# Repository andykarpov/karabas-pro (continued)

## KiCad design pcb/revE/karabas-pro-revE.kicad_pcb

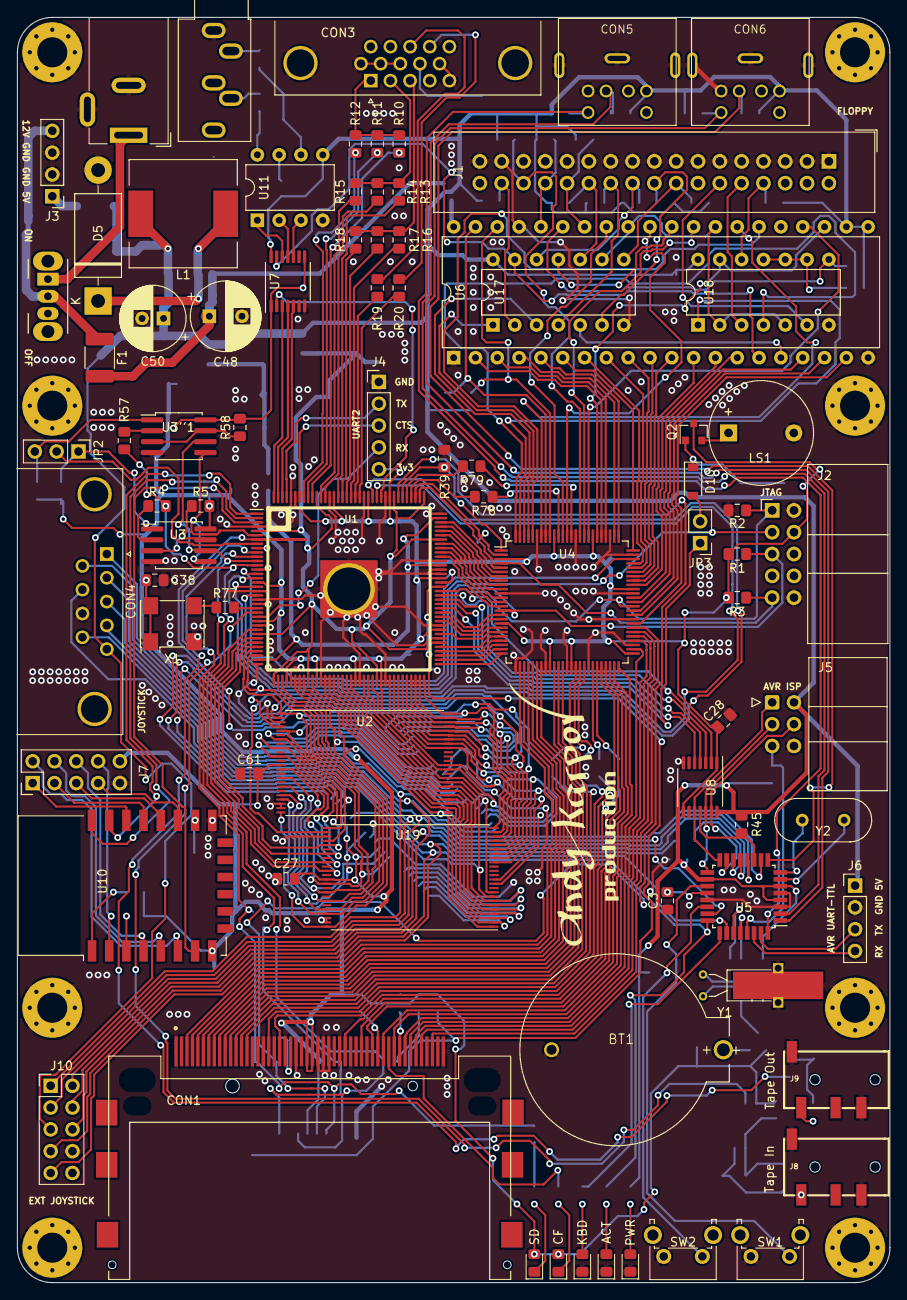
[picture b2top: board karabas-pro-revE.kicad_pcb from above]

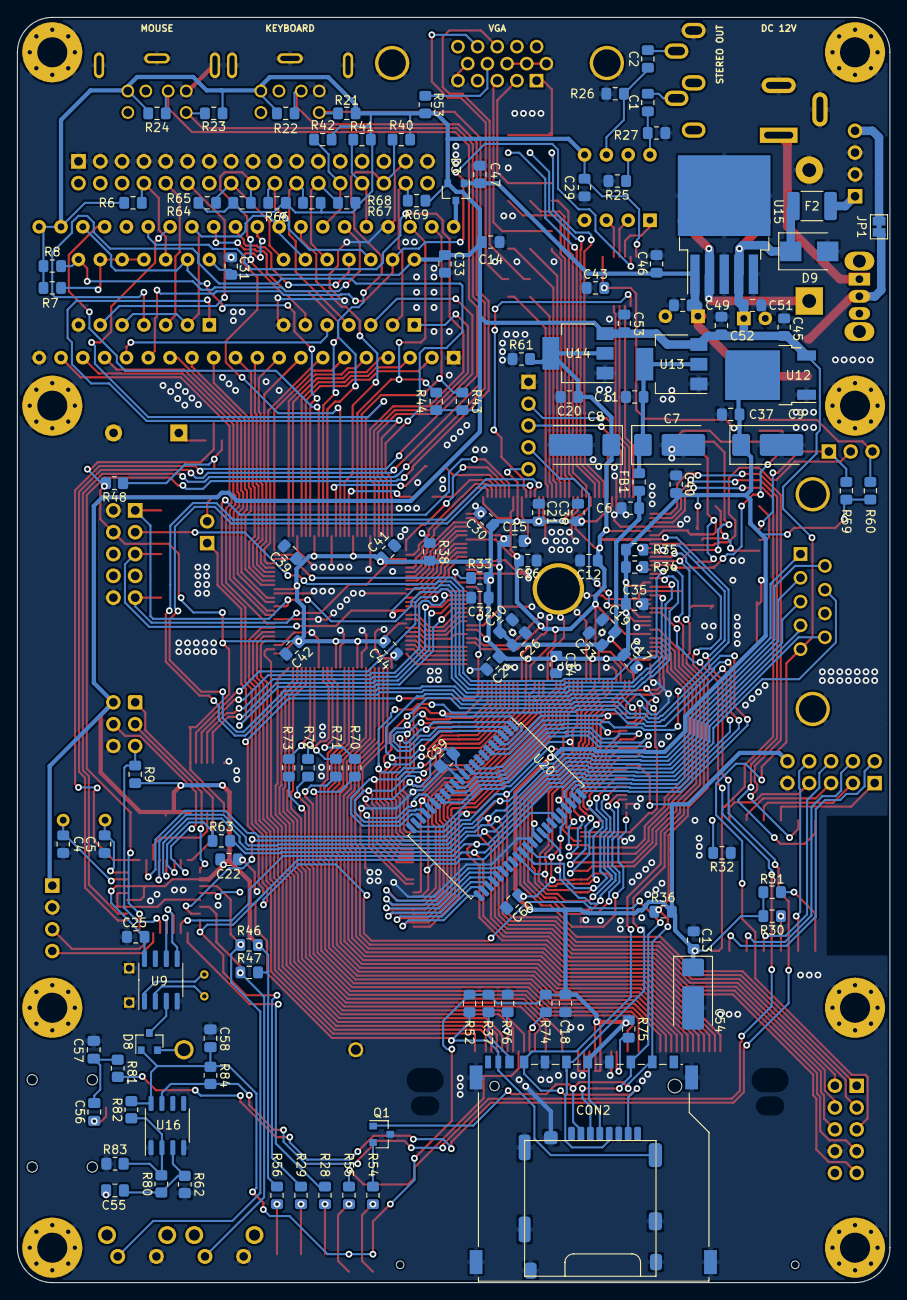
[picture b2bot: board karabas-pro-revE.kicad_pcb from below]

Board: 2 copper layers, 101.6 x 147.3 mm, 217 parts (128 on the bottom side), 272 nets.

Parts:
BT1: 3V; BAT_BS-7-BLUE
C1, C2: 10uF; C_0805_2012Metric_Pad1.15x1.40mm_HandSolder
C3, C10: 1uF; C_0805_2012Metric_Pad1.15x1.40mm_HandSolder
C4, C5: 22p; C_0805_2012Metric_Pad1.15x1.40mm_HandSolder
C6: 1n; C_0805_2012Metric_Pad1.15x1.40mm_HandSolder
C7, C8, C9: 10uF; CP_EIA-7343-31_Kemet-D-uni
C11, C12, C13, C14, C15, C16, C17, C18, C19, C20, C21, C22, C23, C24, C25, C26, C27, C28, C29, C30, C31, C32, C33, C34, C35, C36, C37, C38, C39, C40, C41, C42, C43, C44, C45, C46, C47, C49, C51, C52, C53: 100n; C_0805_2012Metric_Pad1.15x1.40mm_HandSolder
C48: 470uF; CP_Radial_D8.0mm_P3.80mm
C50: 220uF; CP_Radial_D7.5mm_P2.50mm
C54: 100uF; CP_EIA-7343-31_Kemet-D-uni
C55, C56, C58, C59, C60, C61: 100n; C_0805_2012Metric_Pad1.18x1.45mm_HandSolder
C57: 3n3; C_0805_2012Metric_Pad1.18x1.45mm_HandSolder
CON1: CF-CARD; TE_1734451-1-LONG
CON2: SD; SD_TE_2041021-mod
CON3: VGA; DSUB-15-HD_Female_Horizontal_P2.29x1.98mm_EdgePinOffset3.03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
CON4: Joystick; DSUB-9_Male_Horizontal_P2.77x2.84mm_EdgePinOffset7.70mm_Hou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
CON5: Keyboard; MINI_DIN_6_33PRIMARY
CON6: Mouse; MINI_DIN_6_33PRIMARY
CON7: Audio; Jack_3.5mm_CUI_SJ1-3535NG_Horizontal
CON8: 12V; BarrelJack_Wuerth_6941xx301002
CON9: MicroSD'; MICRO_SD_MOLEX
D1: KBD; LED_0805_2012Metric_Pad1.15x1.40mm_HandSolder
D2: ACT; LED_0805_2012Metric_Pad1.15x1.40mm_HandSolder
D3, D8: BAT54C; SOT-23
D4: SD; LED_0805_2012Metric_Pad1.15x1.40mm_HandSolder
D5: 1N5820; D_DO-201AD_P15.24mm_Horizontal
D6: CF; LED_0805_2012Metric_Pad1.15x1.40mm_HandSolder
D7: PWR; LED_0805_2012Metric_Pad1.15x1.40mm_HandSolder
D9: SM6T6V8A; D_SMB
D10: 1N4148W; D_SOD-123
F1, F2: Polyfuse_Small; Fuse_1812_4532Metric_Castellated
FB1: Ferrite_Bead; L_0805_2012Metric_Pad1.15x1.40mm_HandSolder
H1, H2, H3, H4, H5, H6, H7, H8: MountingHole; MountingHole_3.5mm_Pad_Via
J1: Floppy; IDC-Header_2x17_P2.54mm_Vertical
J2: FPGA JTAG; IDC-Header_2x05_P2.54mm_Horizontal
J3: Floppy; PinHeader_1x04_P2.54mm_Vertical
J4: UART2; PinHeader_1x05_P2.54mm_Vertical
J5: AVR JTAG; IDC-Header_2x03_P2.54mm_Horizontal
J6: AVR UART; PinHeader_1x04_P2.54mm_Vertical
J7: ESP-BUS; PinHeader_2x05_P2.54mm_Vertical
J8: Tape In; AUDIO_JACK_3.5MM_SMD_TRRS
J9: Tape Out; AUDIO_JACK_3.5MM_SMD_TRRS
J10: Ext Joystick; PinHeader_2x05_P2.54mm_Vertical
JP1: 12V EN; SolderJumper-2_P1.3mm_Bridged_Pad1.0x1.5mm
JP2: Flash 1/2; PinHeader_1x03_P2.54mm_Vertical
JP3: Beeper enabled; PinHeader_1x02_P2.54mm_Vertical
L1: 68uH; L_12x12mm_H6mm
LS1: Beeper; Buzzer_12x9.5RM7.6
Q1: BC856; SOT-23
Q2: BC847; SOT-23
R1, R2, R3: 2k4; R_0805_2012Metric_Pad1.15x1.40mm_HandSolder
R4, R57, R77, R78, R79: 27; R_0805_2012Metric_Pad1.15x1.40mm_HandSolder
R5, R9, R30, R31, R33, R34, R35, R36, R37, R38, R39, R40, R41, R42, R43, R44, R45, R46, R47, R52, R58, R59, R60: 10k; R_0805_2012Metric_Pad1.15x1.40mm_HandSolder
R6, R11, R14, R17, R74, R75, R76: 1k; R_0805_2012Metric_Pad1.15x1.40mm_HandSolder
R7, R8, R21, R22, R23, R24: 4k7; R_0805_2012Metric_Pad1.15x1.40mm_HandSolder
R10, R13, R16: 2k; R_0805_2012Metric_Pad1.15x1.40mm_HandSolder
R12, R15, R18: 510; R_0805_2012Metric_Pad1.15x1.40mm_HandSolder
R19, R20: 75; R_0805_2012Metric_Pad1.15x1.40mm_HandSolder
R25: 820; R_0805_2012Metric_Pad1.15x1.40mm_HandSolder
R26, R27: 750; R_0805_2012Metric_Pad1.15x1.40mm_HandSolder
R28, R29, R54, R55, R56: 470; R_0805_2012Metric_Pad1.15x1.40mm_HandSolder
R32: 33; R_0805_2012Metric_Pad1.15x1.40mm_HandSolder
R48: 15k*; R_0805_2012Metric_Pad1.20x1.40mm_HandSolder
R53: X*; R_0805_2012Metric_Pad1.15x1.40mm_HandSolder
R61: 300; R_0805_2012Metric_Pad1.15x1.40mm_HandSolder
R62: 1M; R_0805_2012Metric_Pad1.20x1.40mm_HandSolder
R63, R70, R71, R72, R73: 100; R_0805_2012Metric_Pad1.15x1.40mm_HandSolder
R64, R65, R66, R67, R68, R69: 330; R_0805_2012Metric_Pad1.15x1.40mm_HandSolder
R80: 5k1; R_0805_2012Metric_Pad1.20x1.40mm_HandSolder
R81: 33k; R_0805_2012Metric_Pad1.20x1.40mm_HandSolder
R82, R83, R84: 1k; R_0805_2012Metric_Pad1.20x1.40mm_HandSolder
SW1, SW2: SW_Push; SW_Tactile_SPST_Angled_PTS645Vx58-2LFS
SW4: SW_SPST; SW_CuK_OS102011MA1QN1_SPDT_Angled
U1: EP4CE10E22C8N; ALTERA-QFP-145
U2, U19: CY62167EV30LL; TSOP-I-48_18.4x12mm_P0.5mm
U3, U3''1: W25Q16; SOIC-8_5.23x5.23mm_P1.27mm-LONG
U4: EPM3128ATC100-10N; LQFP-100_14x14mm_P0.5mm
U5: ATMEGA328-AU; TQFP-32_7x7mm_P0.8mm
U6: MB8877A; DIP-40_W15.24mm
U7, U8: TXB0104PW; TSSOP-14_4.4x5mm_P0.65mm
U9: DS1307Z+; SOIC-8_3.9x4.9mm_P1.27mm
U10: ESP-12E
U11: TDA1543; DIP-8_W7.62mm
U12: AMS1117-3.3; TO-252-2
U13: AMS1117-2.5; SOT-223-3_TabPin2
U14: AMS1117-1.2; SOT-223-3_TabPin2
U15: LM2596S-5; TO-263-5_TabPin3
U16: LM311; SO-8_3.9x4.9mm_P1.27mm
U17: 74LS06; DIP-14_W7.62mm
U18: 74LS38; DIP-14_W7.62mm
U20: BS62LV1600; TSOP-II-44_10.16x18.41mm_P0.8mm
X1: SG-7050CAN; Oscillator_SMD_SeikoEpson_SG8002CA-4Pin_7.0x5.0mm
Y1: 32768Hz; Crystal_AT310_D3.0mm_L10.0mm_Horizontal_1EP_style2
Y2: 16MHz; Crystal_HC49-U_Vertical

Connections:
+12V: C46.1, C47.1, C48.1, C49.1, D3.1, F1.2, U15.1
/ASDO: U1.6, U3.5, U3''1.5
/AVR_MISO: J5.1, U5.16, U8.10
/AVR_MOSI: J5.4, U5.15, U8.13
/AVR_RX: J6.4, U5.30
/AVR_SCK: J5.3, U5.17, U8.12
/AVR_TX: J6.3, U5.31
/AVR_XT1: C4.2, U5.7, Y2.1
/AVR_XT2: C5.2, U5.8, Y2.2
/B: CON3.3, R16.2, R17.2, R18.2
/BEEPER: JP3.1, U1.86
/BTN1: R46.1, SW1.1, U5.19
/BTN2: R47.1, SW2.1, U5.22
/CLK_50MHZ: R77.2, U1.23
/CONF_DONE: R33.1, U1.92
/CPLD_CLK: R79.2, U1.113
/CPLD_CLK2: R78.2, U1.112
/D0: U4.72, U6.7
/D1: U4.71, U6.8
/D2: U4.70, U6.9
/D3: U4.69, U6.10
/D4: U4.68, U6.11
/D5: U4.67, U6.12
/D6: U4.64, U6.13
/D7: U4.63, U6.14
/DATA0: CON2.7, CON9.7, R4.2, R57.2, U1.13
/DCLK: CON2.5, CON9.5, U1.12, U3.6, U3''1.6
/ESP_ADC: J7.8, U10.2
/ESP_GPIO0: J7.5, U10.18
/ESP_GPIO2: J7.7, U10.17
/ESP_GPIO4: J7.3, U10.19
/ESP_GPIO5: J7.1, U10.20
/ESP_GPIO12: J7.2, U10.6
/ESP_GPIO14: J7.4, U10.5
/ESP_GPIO16: J7.6, U10.4
/FDC_A0: U4.76, U6.5
/FDC_A1: U4.75, U6.6
/FDC_CLK: U4.83, U6.24
/FDC_DIR: U6.16, U17.5
/FDC_DRQ: R44.1, U4.92, U6.38
/FDC_DS0: U4.99, U18.1
/FDC_DS1: U4.100, U18.4
/FDC_HLT: U4.81, U6.23, U18.13
/FDC_INTRQ: R43.1, U4.93, U6.39
/FDC_IP: R8.2, U6.35, U18.8
/FDC_RCLK: U4.96, U6.26
/FDC_RDY: U6.28, U6.32, U17.9, U18.2, U18.5
/FDC_SIDE: J1.32, R69.2, U17.2
/FDC_SL: U4.61, U6.17
/FDC_SR: U4.60, U6.18
/FDC_STEP: U6.15, U7.13, U17.13
/FDC_TR43: U4.84, U6.29
/FDC_WD: U4.88, U6.31
/FDC_WDATA: U4.98, U17.3
/FDC_WF_DE: U4.89, U6.33
/FDC_WGATE: U6.30, U17.11
/G: CON3.2, R13.2, R14.2, R15.2
/HS: CON3.13, R19.1
/I2C_SCL: U5.28, U9.6
/I2C_SDA: U5.27, U9.5
/JOY_DOWN: CON4.2, J10.2, U5.12
/JOY_FIRE1: CON4.6, J10.6, U5.23
/JOY_FIRE2: CON4.9, J10.9, U5.26
/JOY_LEFT: CON4.3, J10.3, U5.13
/JOY_R2: CON4.4, J10.4, R63.2
/JOY_RIGHT: R63.1, U5.14
/JOY_UP: CON4.1, J10.1, U5.10
/L1: D1.2, R28.2
/L2: D2.2, R29.2
/L3: D7.2, R56.2
/L4: D4.1, R54.2
/L5: D6.1, R55.2
/LAVR_MISO: U1.87, U8.5
/LAVR_MOSI: U1.90, U8.2
/LAVR_SCK: U1.89, U8.3
/LED1: R28.1, U5.25
/LED2: CON4.7, J10.7, R29.1, U5.24
/LED_BUSY: CON1.45, R55.1
/LFDC_STEP: U1.119, U7.2
/LSND_BS: U1.144, U7.3
/LSND_DAT: U1.142, U7.5
/LSND_WS: U1.143, U7.4
/MA0: U1.33, U2.25, U19.25, U20.5
/MA1: U1.72, U2.24, U19.24, U20.4
/MA2: U1.71, U2.23, U19.23, U20.3
/MA3: U1.70, U2.22, U19.22, U20.2
/MA4: U1.69, U2.21, U19.21, U20.1
/MA5: U1.68, U2.20, U19.20, U20.44
/MA6: U1.67, U2.19, U19.19, U20.43
/MA7: U1.66, U2.18, U19.18, U20.42
/MA8: U1.58, U2.8, U19.8, U20.39
/MA9: U1.55, U2.7, U19.7, U20.28
/MA10: U1.54, U2.6, U19.6, U20.27
/MA11: U1.53, U2.5, U19.5, U20.26
/MA12: U1.52, U2.4, U19.4, U20.25
/MA13: U1.51, U2.3, U19.3, U20.24
/MA14: U1.50, U2.2, U19.2, U20.23
/MA15: U1.49, U2.1, U19.1, U20.22
/MA16: U1.46, U2.48, U19.48, U20.21
/MA17: U1.65, U2.17, U19.17, U20.20
/MA18: U1.64, U2.16, U19.16, U20.19
/MA19: U1.59, U2.9, U19.9, U20.18
/MA20: U1.44, U2.45, U19.45, U20.16
/MD0: U1.32, U2.29, U19.29, U20.9
/MD1: U1.31, U2.31, U19.31, U20.10
/MD2: U1.30, U2.33, U19.33, U20.13
/MD3: U1.28, U2.35, U19.35, U20.14
/MD4: U1.38, U2.38, U19.38, U20.31
/MD5: U1.39, U2.40, U19.40, U20.32
/MD6: U1.42, U2.42, U19.42, U20.35
/MD7: U1.43, U2.44, U19.44, U20.36
/NCONFIG: R34.1, U1.14
/NCSO: JP2.2, U1.8
/NCSO1: JP2.1, R59.1, U3.1
/NCSO2: JP2.3, R60.1, U3''1.1
/NSTATUS: R35.1, U1.9
/PS2_KB_CLK: CON5.5, R21.1, U5.32
/PS2_KB_DATA: CON5.1, R22.1, U5.2
/PS2_MS_CLK: CON6.5, R23.1, U5.1
/PS2_MS_DATA: CON6.1, R24.1, U5.9
/R: CON3.1, R10.2, R11.2, R12.2
/SA0: U1.110, U4.5
/SA1: U1.106, U4.6
/SD0: U1.105, U4.7
/SD1: U1.104, U4.8
/SD2: U1.103, U4.9
/SD3: U1.101, U4.10
/SD4: U1.100, U4.12
/SD5: U1.99, U4.13
/SD6: U1.98, U4.14
/SD7: U1.85, U4.16
/SD8: U1.84, U4.17
/SD9: U1.83, U4.19
/SD10: U1.80, U4.20
/SD11: U1.77, U4.21
/SD12: U1.76, U4.22
/SD13: U1.75, U4.23
/SD14: U1.74, U4.24
/SD15: U1.73, U4.25
/SDIR: R38.1, U1.111, U4.2
/SD_DI: CON2.2, CON9.3, U1.115
/SND_BS: U7.12, U11.1
/SND_DAT: U7.10, U11.3
/SND_L: C2.2, CON7.T
/SND_R: C1.2, CON7.R
/SND_WS: U7.11, U11.2
/TCK: J2.1, R2.2, U1.16, U4.62
/TDI: J2.9, R3.1, U4.4
/TDI1: U1.15, U4.73
/TDO: J2.3, U1.20
/TMS: J2.5, R1.1, U1.18, U4.15
/UART2_CTS: J4.3, U1.138
/UART2_RX: J4.4, U1.25
/UART2_TX: J4.2, U1.141
/UART_CTS: U1.3, U10.7
/UART_RX: U1.2, U10.22
/UART_TX: U1.1, U10.21
/VGA_B0: R16.1, U1.126
/VGA_B1: R17.1, U1.127
/VGA_B2: R18.1, U1.128
/VGA_G0: R13.1, U1.129
/VGA_G1: R14.1, U1.132
/VGA_G2: R15.1, U1.133
/VGA_HS: R19.2, U1.125
/VGA_R0: R10.1, U1.135
/VGA_R1: R11.1, U1.136
/VGA_R2: R12.1, U1.137
/VGA_VS: R20.2, U1.124
/VS: CON3.14, R20.1
/WA0: CON1.20, U4.49
/WA1: CON1.19, U4.48
/WA2: CON1.18, U4.47
/WD0: CON1.21, U4.50
/WD1: CON1.22, U4.52
/WD2: CON1.23, U4.55
/WD3: CON1.2, U4.27
/WD4: CON1.3, U4.29
/WD5: CON1.4, U4.31
/WD6: CON1.5, U4.35
/WD7: CON1.6, U4.37
/WD8: CON1.47, U4.54
/WD9: CON1.48, U4.56
/WD10: CON1.49, U4.57
/WD11: CON1.27, U4.28
/WD12: CON1.28, U4.30
/WD13: CON1.29, U4.32
/WD14: CON1.30, U4.36
/WD15: CON1.31, U4.40
/~AVR_CS: R45.1, U5.11, U8.11
/~AVR_RESET: J5.5, R9.1, U5.29
/~FDC_CS: U4.79, U6.3
/~FDC_DIR: J1.18, R65.2, U17.6
/~FDC_DRIVE0: J1.10, U18.3
/~FDC_DRIVE1: J1.12, U18.6
/~FDC_INDEX: J1.8, R6.2, U18.12
/~FDC_MOTOR: J1.16, R64.2, U17.8
/~FDC_RAWR: U4.94, U6.27
/~FDC_RDATA: J1.30, R40.1, U4.85
/~FDC_RST: U4.58, U6.19
/~FDC_SIDE: U4.97, U17.1
/~FDC_STEP: J1.20, R66.2, U17.12
/~FDC_TR00: J1.26, R42.1, U6.34
/~FDC_WDATA: J1.22, R67.2, U17.4
/~FDC_WGATE: J1.24, R68.2, U17.10
/~FDC_WPRT: J1.28, R41.1, U6.36
/~LAVR_CS: U1.88, U8.4
/~LWCS0: R70.1, U4.41
/~LWCS1: R71.1, U4.42
/~LWRD: R72.1, U4.44
/~LWWR: R73.1, U4.45
/~MRD: U1.34, U2.28, U19.28, U20.41
/~MWR: U1.60, U2.11, U19.11, U20.17
/~RAMCE1: U1.121, U2.26
/~RAMCE2: U1.120, U19.26
/~RAMCE3: U1.7, U20.6
/~RD: U4.77, U6.4
/~RESET: R39.1, U1.114, U4.1
/~SD_CS: CON2.1, CON9.2, Q1.1, R36.1, U1.11
/~SD_DET: CON2.10, CON9.9, R52.1, U1.91
/~WCS0: CON1.7, R70.2
/~WCS1: CON1.32, R71.2
/~WR: U4.80, U6.2
/~WRD: CON1.34, R72.2
/~WRESET: CON1.41, U4.46
/~WWR: CON1.35, R73.2
GND: BT1.2, C3.1, C4.1, C5.1, C6.2, C7.2, C8.2, C9.2, C10.2, C11.2, C12.2, C13.2, C14.2, C15.2, C16.2, C17.2, C18.2, C19.2, C20.2, C21.2, C22.2, C23.2, C24.2, C25.2, C26.2, C27.2, C28.2, C29.2, C30.2, C31.2, C32.2, C33.2, C34.2, C35.2, C36.2, C37.2, C38.2, C39.2, C40.2, C41.2, C42.2, C43.2, C44.2, C45.2, C46.2, C47.2, C48.2, C49.2, C50.2, C51.2, C52.2, C53.2, C54.2, C57.1, C58.2, C59.2, C60.2, C61.2, CON1.1, CON1.8, CON1.9, CON1.10, CON1.11, CON1.12, CON1.14, CON1.15, CON1.16, CON1.17, CON1.39, CON1.50, CON2.3, CON2.6, CON2.12, CON2.13, CON3.0, CON3.5, CON3.6, CON3.7, CON3.8, CON3.10, CON4.0, CON4.8, CON5.3, CON5.GND, CON6.3, CON6.GND, CON7.S, CON8.2, CON8.3, CON9.6, CON9.10, CON9.11, CON9.12, CON9.13, CON9.14, CON9.15, D1.1, D2.1, D5.2, D7.1, D9.2, H1.1, H2.1, H3.1, H4.1, H5.1, H6.1, H7.1, H8.1, J1.1, J1.3, J1.5, J1.7, J1.9, J1.11, J1.13, J1.15, J1.17, J1.19, J1.21, J1.23, J1.25, J1.27, J1.29, J1.31, J1.33, J2.2, J2.10, J3.2, J3.3, J4.1, J5.6, J6.2, J7.9, J8.R2, J8.S, J9.R2, J9.S, J10.8, LS1.2, Q1.3, R2.1, R25.2, R26.2, R27.2, R32.1, R39.2, R61.1, R62.2, R76.2, R83.2, SW1.2, SW2.2, U1.4, U1.19, U1.21, U1.22, U1.27, U1.36, U1.41, U1.48, U1.57, U1.63, U1.79, U1.82, U1.94, U1.95, U1.97, U1.108, U1.118, U1.123, U1.131, U1.140, U1.145, U2.27, U2.46, U2.47, U3.4, U3''1.4, U4.11, U4.26, U4.33, U4.38, U4.43, U4.53, U4.59, U4.65, U4.74, U4.78, U4.86, U4.95, U5.3, U5.5, U5.21, U6.1, U6.20, U6.37, U7.7, U8.7, U9.4, U10.15, U11.4, U12.1, U13.1, U14.1, U15.3, U15.5, U16.1, U16.4, U17.7, U18.7, U19.27, U19.46, U19.47, U20.12, U20.34, X1.2, Y1.3
unnamed: BT1.1, D8.2
unnamed: C1.1, R27.1, U11.8
unnamed: C2.1, R26.1, U11.6
unnamed: C3.2, U5.20
unnamed: C7.1, C11.1, FB1.1, U13.2
unnamed: C55.1, J8.T
unnamed: C55.2, R62.1, R80.1, U16.3
unnamed: C56.1, J9.T
unnamed: C56.2, C57.2, R81.1
unnamed: CON1.36, R75.2
unnamed: CON1.44, R74.2
unnamed: CON1.46, R76.1
unnamed: CON2.8, R37.2
unnamed: CON3.9, R53.2
unnamed: CON8.1, SW4.1
unnamed: D3.3, U6.40
unnamed: D5.1, L1.1, U15.2
unnamed: D8.3, U9.3
unnamed: D10.1, Q2.1, R48.1
unnamed: D10.2, JP3.2
unnamed: F1.1, JP1.2, SW4.2
unnamed: F2.1, J3.1
unnamed: J3.4, JP1.1
unnamed: LS1.1, Q2.2
unnamed: Q1.2, R54.1
unnamed: R4.1, U3.2
unnamed: R5.1, U3.3, U3.7
unnamed: R7.2, U18.9, U18.10, U18.11
unnamed: R25.1, U11.7
unnamed: R30.1, U10.3
unnamed: R31.1, U10.1
unnamed: R32.2, U10.16
unnamed: R57.1, U3''1.2
unnamed: R58.1, U3''1.3, U3''1.7
unnamed: R77.1, X1.3
unnamed: R78.1, U4.90
unnamed: R79.1, U4.87
unnamed: R80.2, R82.2, R83.1, U16.2
unnamed: U9.1, Y1.2
unnamed: U9.2, Y1.1
TAPE_IN: R84.2, U1.24, U16.7
TAPE_OUT: R81.2, U1.10
VCC: C14.1, C22.1, C25.1, C29.1, C31.1, C33.1, C45.1, C50.1, C51.1, C52.1, C53.1, CON4.5, CON5.4, CON6.4, D3.2, D9.1, F2.2, J5.2, J6.1, J10.5, L1.2, R6.1, R7.1, R8.1, R9.2, R21.2, R22.2, R23.2, R24.2, R40.2, R41.2, R42.2, R43.2, R44.2, R45.2, R46.2, R47.2, R53.1, R56.1, R64.1, R65.1, R66.1, R67.1, R68.1, R69.1, U5.4, U5.6, U5.18, U6.21, U6.22, U7.14, U8.14, U9.8, U11.5, U12.3, U13.3, U14.3, U15.4, U17.14, U18.14
VCC1_2: C8.1, C12.1, C16.1, C20.1, R61.2, U1.5, U1.29, U1.37, U1.45, U1.61, U1.78, U1.102, U1.109, U1.116, U1.134, U14.2
VCC2_5: C6.1, C10.1, C15.1, C19.1, C23.1, C26.1, FB1.2, U1.35, U1.96, U1.107
VCC3_3: C9.1, C13.1, C17.1, C18.1, C21.1, C24.1, C27.1, C28.1, C30.1, C32.1, C34.1, C35.1, C36.1, C37.1, C38.1, C39.1, C40.1, C41.1, C42.1, C43.1, C44.1, C54.1, C58.1, C59.1, C60.1, C61.1, CON1.13, CON1.38, CON2.4, CON9.4, D4.2, D6.2, D8.1, J2.4, J4.5, J7.10, Q2.3, R1.2, R3.2, R5.2, R30.2, R31.2, R33.2, R34.2, R35.2, R36.2, R37.1, R38.2, R48.2, R52.2, R58.2, R59.2, R60.2, R74.1, R75.1, R82.1, R84.1, U1.17, U1.26, U1.40, U1.47, U1.56, U1.62, U1.81, U1.93, U1.117, U1.122, U1.130, U1.139, U2.12, U2.37, U3.8, U3''1.8, U4.3, U4.18, U4.34, U4.39, U4.51, U4.66, U4.82, U4.91, U7.1, U7.8, U8.1, U8.8, U10.8, U12.2, U16.8, U19.12, U19.37, U20.11, U20.33, U20.40, X1.1, X1.4

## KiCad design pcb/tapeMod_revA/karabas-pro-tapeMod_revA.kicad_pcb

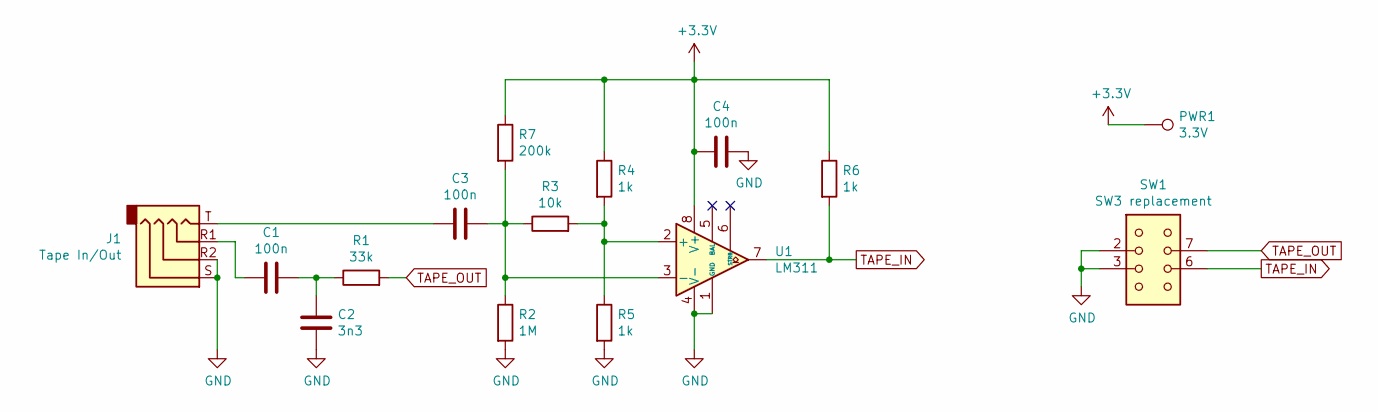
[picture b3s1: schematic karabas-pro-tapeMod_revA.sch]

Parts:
C1, C3, C4: 100n; C_0805_2012Metric_Pad1.18x1.45mm_HandSolder
C2: 3n3; C_0805_2012Metric_Pad1.18x1.45mm_HandSolder
J1: Tape In/Out; AUDIO_JACK_3.5MM_SMD_TRRS
PWR1: 3.3V; TestPoint_Pad_2.0x2.0mm
R1: 33k; R_0805_2012Metric_Pad1.20x1.40mm_HandSolder
R2: 1M; R_0805_2012Metric_Pad1.20x1.40mm_HandSolder
R3: 10k; R_0805_2012Metric_Pad1.20x1.40mm_HandSolder
R4, R5, R6: 1k; R_0805_2012Metric_Pad1.20x1.40mm_HandSolder
R7: 200k; R_0805_2012Metric_Pad1.20x1.40mm_HandSolder
SW1: SW3 replacement; SW_DIP_SPSTx04_Piano_TAPE_MOD
U1: LM311; SO-8_3.9x4.9mm_P1.27mm

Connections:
+3V3: C4.1, PWR1.1, R4.1, R6.1, R7.1, U1.8 (V+); also elsewhere on the board
GND: C2.1, C4.2, J1.R2, J1.S, R2.2, R5.2, SW1.2, SW1.3, U1.1 (GND), U1.4 (V-)
unnamed: C1.1, J1.R1
unnamed: C1.2, C2.2, R1.1
unnamed: C3.1, J1.T
unnamed: C3.2, R2.1, R3.1, R7.2, U1.3 (-)
unnamed: R3.2, R4.2, R5.1, U1.2 (+)
TAPE_IN: R6.2, SW1.6, U1.7
TAPE_OUT: R1.2, SW1.7

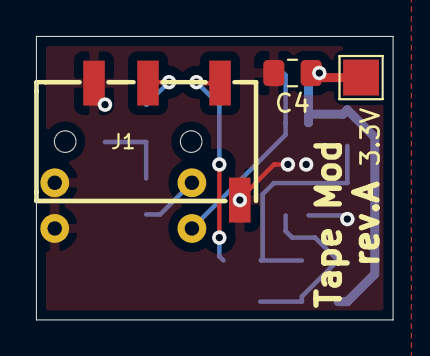
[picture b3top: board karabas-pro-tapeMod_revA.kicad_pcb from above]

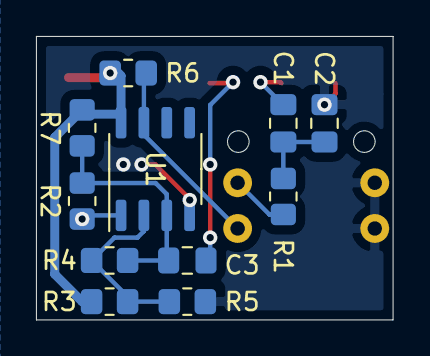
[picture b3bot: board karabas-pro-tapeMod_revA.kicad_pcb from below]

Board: 2 copper layers, 19.8 x 15.7 mm, 15 parts (11 on the bottom side), 9 nets.

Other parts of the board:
3.3V: 3.3V; TestPoint_Pad_2.0x2.0mm

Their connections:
+3V3: 3.3V.1; also elsewhere on the board

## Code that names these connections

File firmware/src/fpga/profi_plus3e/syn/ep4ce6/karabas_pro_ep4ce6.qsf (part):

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set_global_assignment -name LAST_QUARTUS_VERSION "13.0 SP1"

#==================CLK===========================
set_location_assignment PIN_23 -to CLK_50MHZ

#==================SRAM=========================
set_location_assignment PIN_28 -to SRAM_D[3]
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set_location_assignment PIN_72 -to SRAM_A[1]

#=================FLASH=========================
set_location_assignment PIN_6 -to ASDO
set_location_assignment PIN_13 -to DATA0
set_location_assignment PIN_12 -to DCLK
set_location_assignment PIN_8 -to NCSO
set_instance_assignment -name IO_MAXIMUM_TOGGLE_RATE "0 MHz" -to DCLK

#=================SD CARD=======================
set_location_assignment PIN_11 -to SD_NCS

#=================AVR===========================
set_location_assignment PIN_87 -to AVR_MISO
set_location_assignment PIN_88 -to AVR_NCS
set_location_assignment PIN_89 -to AVR_SCK
set_location_assignment PIN_90 -to AVR_MOSI

#=================UART==========================
set_location_assignment PIN_1 -to UART_TX
set_location_assignment PIN_2 -to UART_RX
set_location_assignment PIN_3 -to UART_CTS

#=================I2S===========================
set_location_assignment PIN_144 -to SND_BS
set_location_assignment PIN_143 -to SND_WS
set_location_assignment PIN_142 -to SND_DAT

#=================VGA===========================
set_location_assignment PIN_137 -to VGA_R[2]
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set_location_assignment PIN_128 -to VGA_B[2]
set_location_assignment PIN_127 -to VGA_B[1]
set_location_assignment PIN_126 -to VGA_B[0]
set_location_assignment PIN_125 -to VGA_HS
set_location_assignment PIN_124 -to VGA_VS

#================CPLD===========================
set_location_assignment PIN_114 -to NRESET
set_location_assignment PIN_113 -to CPLD_CLK
set_location_assignment PIN_112 -to CPLD_CLK2
set_location_assignment PIN_111 -to SDIR
set_location_assignment PIN_110 -to SA[0]
set_location_assignment PIN_106 -to SA[1]
set_location_assignment PIN_105 -to SD[0]
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

set_location_assignment PIN_91 -to SD_NDET
set_location_assignment PIN_119 -to FDC_STEP
set_location_assignment PIN_115 -to SD_MOSI

set_parameter -name build_version 00000000
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

set_location_assignment PIN_7 -to PIN_7
set_location_assignment PIN_10 -to TAPE_OUT
set_location_assignment PIN_24 -to TAPE_IN
set_location_assignment PIN_25 -to PIN_25
set_location_assignment PIN_86 -to BUZZER

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
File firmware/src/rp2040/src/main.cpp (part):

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#include "PS2Mouse.h"
#include <GyverFIFO.h>

#define SD_CONFIG  SdSpiConfig(PIN_SD_CS, SHARED_SPI, SD_SCK_MHZ(8), &SPI) // SD1 SPI Settings
SPISettings settingsA(SD_SCK_MHZ(8), MSBFIRST, SPI_MODE0); // MCU SPI settings

File file1, file2;
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  pinMode(PIN_CONF_NSTATUS, INPUT_PULLUP);
  pinMode(PIN_CONF_NCONFIG, OUTPUT);
  digitalWrite(PIN_CONF_NCONFIG, HIGH);
  pinMode(PIN_CONF_DONE, INPUT_PULLUP);
  pinMode(PIN_CONF_CLK, OUTPUT);
  digitalWrite(PIN_CONF_CLK, HIGH);
  pinMode(PIN_CONF_DATA, INPUT_PULLUP);

  // dedicated SD CS to access from MCU via shared FPGA
  pinMode(PIN_SD_CS, OUTPUT);
  digitalWrite(PIN_SD_CS, HIGH);

  pinMode(PIN_TP3, INPUT_PULLUP);
  pinMode(PIN_TP4, INPUT_PULLUP);
  pinMode(PIN_TP5, INPUT_PULLUP);

  // I2C
  Wire.setSDA(PIN_I2C_SDA);
  Wire.setSCL(PIN_I2C_SCL);
  Wire.setClock(100000);
  Wire.begin();

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  d_begin(115200);
  d_println("Karabas Pro RP2040 firmware");

  pinMode(PIN_UART_CTS, OUTPUT); digitalWrite(PIN_UART_CTS, LOW); // CTS bypass if enabled
  Serial1.begin(115200); // esp uart

  sega.begin(PIN_JOY_SCK, PIN_JOY_LOAD, PIN_JOY_DATA, PIN_JOY_P7);

  pinMode(PIN_BTN1, INPUT_PULLUP);
  pinMode(PIN_BTN2, INPUT_PULLUP);
  pinMode(PIN_LED1, OUTPUT); digitalWrite(PIN_LED1, HIGH);
  pinMode(PIN_LED2, OUTPUT); digitalWrite(PIN_LED2, HIGH);

  zxrtc.begin(spi_send, on_time);
  zxosd.begin(spi_send);
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    ps2_pressed[i] = 0;
  }
  ps2_pressed_size = 0;
  kbd.begin(PIN_PS2_KB_DATA, PIN_PS2_KB_CLK, &ps2_int);
  mouse.begin(PIN_PS2_MS_CLK, PIN_PS2_MS_DATA);
  mouse_present = mouse.streamInitialize();
  mouse_timer.reset();
  mouse_tries = MOUSE_INIT_TRIES;
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	while (queue_try_remove(&spi_event_queue, &packet)) {
    // skip keyboard transmission when osd is active
    if (packet.cmd == CMD_USB_KBD) {
      digitalWrite(PIN_LED2, !(usb_keyboard_report.modifier != 0 || usb_keyboard_report.keycode[0] != 0));
      if (packet.addr == 1 && packet.data != 0) {
          on_keyboard();
      }
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  sd1.end();
  has_sd = false;
  SPI.end(); SPI.begin(false); // reinit SPI
  digitalWrite(PIN_SD_CS, HIGH); // disabling SD CS

  fpga_send(filename);
  spi_send(CMD_INIT_START, 0, 0);
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  has_sd = false;
  if (core.sd_enable) {
    d_println("Trying to mount SD card");
    has_sd = sd1.begin(SdSpiConfig(PIN_SD_CS, SHARED_SPI, SD_SCK_MHZ(8), &SPI));
    if (has_sd) {
      d_println("SD card mounted");
      update_cores_from_sd();
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    sd1.end();
    has_sd = false;
  }
  digitalWrite(PIN_SD_CS, HIGH); // disabling SD CS
  SPI.end(); SPI.begin(false); // reinit SPI
  is_configuring = false;
  d_println("FPGA configuration finished");
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  delay(2);
  digitalWrite(PIN_CONF_NCONFIG, HIGH);

  // wait for NSTATUS = 1
  uint32_t i = 100;
  while (i-- > 0 && digitalRead(PIN_CONF_NSTATUS) != HIGH)
    delay(10);
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  d_print("Waiting for CONF_DONE... ");

  i = 10;
  while (i-- > 0 && digitalRead(PIN_CONF_DONE) != HIGH)
    delay(10);

  if (digitalRead(PIN_CONF_DONE) == HIGH) {
    d_println("Done");
  } else {
    d_println("Failed");
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  switch (cmd) {
    case CMD_UART_FIFO_STATUS : 
      esp_fifo_full = bitRead(data, 0); // rx esp fifo on fpga side
      digitalWrite(PIN_UART_CTS, esp_fifo_full); // set hw cts 0/1
      usb_fifo_full = bitRead(data, 1); // rx usb fifo on fpga side
      //d_print("ESP FIFO "); if (esp_fifo_full) d_println("full") else d_println("empty");
      //d_print("USB FIFO "); if (usb_fifo_full) d_println("full") else d_println("empty");
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
bool btn_read(uint8_t num) {
  if (num == 0) { 
    return !digitalRead(PIN_BTN1);
  } else {
    return !digitalRead(PIN_BTN2);
  }
}

void led_write(uint8_t num, bool on) {
  if (num == 0) { 
    digitalWrite(PIN_LED1, !on);
  } else {
    digitalWrite(PIN_LED2, !on);
  }
}

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
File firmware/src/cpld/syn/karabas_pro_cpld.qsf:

# -------------------------------------------------------------------------- #
#
# Copyright (C) 1991-2013 Altera Corporation
# Your use of Altera Corporation's design tools, logic functions 
# and other software and tools, and its AMPP partner logic 
# functions, and any output files from any of the foregoing 
# (including device programming or simulation files), and any 
# associated documentation or information are expressly subject 
# to the terms and conditions of the Altera Program License 
# Subscription Agreement, Altera MegaCore Function License 
# Agreement, or other applicable license agreement, including, 
# without limitation, that your use is for the sole purpose of 
# programming logic devices manufactured by Altera and sold by 
# Altera or its authorized distributors.  Please refer to the 
# applicable agreement for further details.
#
# -------------------------------------------------------------------------- #
#
# Quartus II 32-bit
# Version 13.0.1 Build 232 06/12/2013 Service Pack 1 SJ Web Edition
# Date created = 15:44:26  June 08, 2020
#
# -------------------------------------------------------------------------- #
#
# Notes:
#
# 1) The default values for assignments are stored in the file:
#		test_karabas_fpga_fdd_assignment_defaults.qdf
#    If this file doesn't exist, see file:
#		assignment_defaults.qdf
#
# 2) Altera recommends that you do not modify this file. This
#    file is updated automatically by the Quartus II software
#    and any changes you make may be lost or overwritten.
#
# -------------------------------------------------------------------------- #


set_global_assignment -name FAMILY MAX3000A
set_global_assignment -name DEVICE "EPM3128ATC100-10"
set_global_assignment -name TOP_LEVEL_ENTITY karabas_pro_cpld
set_global_assignment -name ORIGINAL_QUARTUS_VERSION "13.0 SP1"
set_global_assignment -name PROJECT_CREATION_TIME_DATE "15:44:26  JUNE 08, 2020"
set_global_assignment -name LAST_QUARTUS_VERSION "13.0 SP1"
set_global_assignment -name PROJECT_OUTPUT_DIRECTORY ./
set_global_assignment -name ERROR_CHECK_FREQUENCY_DIVISOR "-1"
set_global_assignment -name VHDL_FILE ../rtl/karabas_pro_cpld.vhd
set_global_assignment -name STRATIX_DEVICE_IO_STANDARD "2.5 V"
set_instance_assignment -name PARTITION_HIERARCHY root_partition -to | -section_id Top
set_global_assignment -name PARTITION_NETLIST_TYPE SOURCE -section_id Top
set_global_assignment -name PARTITION_FITTER_PRESERVATION_LEVEL PLACEMENT_AND_ROUTING -section_id Top
set_global_assignment -name PARTITION_COLOR 16764057 -section_id Top
set_global_assignment -name MAX7000_DEVICE_IO_STANDARD "3.3-V LVTTL"
set_global_assignment -name SDC_FILE karabas_pro_cpld.sdc
set_location_assignment PIN_27 -to HDD_D[3]
set_location_assignment PIN_28 -to HDD_D[11]
set_location_assignment PIN_29 -to HDD_D[4]
set_location_assignment PIN_30 -to HDD_D[12]
set_location_assignment PIN_31 -to HDD_D[5]
set_location_assignment PIN_32 -to HDD_D[13]
set_location_assignment PIN_35 -to HDD_D[6]
set_location_assignment PIN_36 -to HDD_D[14]
set_location_assignment PIN_37 -to HDD_D[7]
set_location_assignment PIN_40 -to HDD_D[15]
set_location_assignment PIN_41 -to HDD_NCS0
set_location_assignment PIN_42 -to HDD_NCS1
set_location_assignment PIN_44 -to HDD_NRD
set_location_assignment PIN_45 -to HDD_NWR
set_location_assignment PIN_47 -to HDD_A[2]
set_location_assignment PIN_48 -to HDD_A[1]
set_location_assignment PIN_49 -to HDD_A[0]
set_location_assignment PIN_46 -to HDD_NRESET
set_location_assignment PIN_50 -to HDD_D[0]
set_location_assignment PIN_52 -to HDD_D[1]
set_location_assignment PIN_54 -to HDD_D[8]
set_location_assignment PIN_55 -to HDD_D[2]
set_location_assignment PIN_56 -to HDD_D[9]
set_location_assignment PIN_57 -to HDD_D[10]
set_location_assignment PIN_6 -to SA[1]
set_location_assignment PIN_5 -to SA[0]
set_location_assignment PIN_1 -to NRESET
set_location_assignment PIN_87 -to CLK
set_location_assignment PIN_58 -to FDC_NRESET
set_location_assignment PIN_60 -to FDC_SR
set_location_assignment PIN_61 -to FDC_SL
set_location_assignment PIN_63 -to FDC_D[7]
set_location_assignment PIN_64 -to FDC_D[6]
set_location_assignment PIN_67 -to FDC_D[5]
set_location_assignment PIN_68 -to FDC_D[4]
set_location_assignment PIN_69 -to FDC_D[3]
set_location_assignment PIN_70 -to FDC_D[2]
set_location_assignment PIN_71 -to FDC_D[1]
set_location_assignment PIN_72 -to FDC_D[0]
set_location_assignment PIN_75 -to FDC_A[1]
set_location_assignment PIN_76 -to FDC_A[0]
set_location_assignment PIN_77 -to FDC_NRD
set_location_assignment PIN_80 -to FDC_NWR
set_location_assignment PIN_79 -to FDC_NCS
set_location_assignment PIN_81 -to FDC_HLT
set_location_assignment PIN_83 -to FDC_CLK
set_location_assignment PIN_84 -to FDC_TR43
set_location_assignment PIN_85 -to FDC_RDATA
set_location_assignment PIN_88 -to FDC_WD
set_location_assignment PIN_89 -to FDC_WF_DE
set_location_assignment PIN_92 -to FDC_DRQ
set_location_assignment PIN_93 -to FDC_INTRQ
set_location_assignment PIN_94 -to FDC_NRAWR
set_location_assignment PIN_100 -to FDC_DS1
set_location_assignment PIN_99 -to FDC_DS0
set_location_assignment PIN_98 -to FDC_WDATA
set_location_assignment PIN_97 -to FDC_SIDE
set_location_assignment PIN_96 -to FDC_RCLK
set_location_assignment PIN_90 -to CLK2

set_global_assignment -name VHDL_FILE ../rtl/ide_controller.vhd
set_global_assignment -name VHDL_FILE ../rtl/fdd_controller.vhd

set_global_assignment -name MAX7000_OPTIMIZATION_TECHNIQUE AREA
set_global_assignment -name SYNTH_TIMING_DRIVEN_SYNTHESIS OFF
set_global_assignment -name OPTIMIZE_HOLD_TIMING OFF
set_global_assignment -name OPTIMIZE_MULTI_CORNER_TIMING OFF
set_global_assignment -name FITTER_EFFORT "STANDARD FIT"

set_global_assignment -name TIMEQUEST_MULTICORNER_ANALYSIS OFF

set_location_assignment PIN_2 -to SDIR
set_location_assignment PIN_25 -to SD_OUT[7]
set_location_assignment PIN_24 -to SD_OUT[6]
set_location_assignment PIN_23 -to SD_OUT[5]
set_location_assignment PIN_22 -to SD_OUT[4]
set_location_assignment PIN_21 -to SD_OUT[3]
set_location_assignment PIN_20 -to SD_OUT[2]
set_location_assignment PIN_19 -to SD_OUT[1]
set_location_assignment PIN_17 -to SD_OUT[0]
set_location_assignment PIN_16 -to SD_IN[7]
set_location_assignment PIN_14 -to SD_IN[6]
set_location_assignment PIN_13 -to SD_IN[5]
set_location_assignment PIN_12 -to SD_IN[4]
set_location_assignment PIN_10 -to SD_IN[3]
set_location_assignment PIN_9 -to SD_IN[2]
set_location_assignment PIN_8 -to SD_IN[1]
set_location_assignment PIN_7 -to SD_IN[0]

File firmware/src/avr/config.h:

#ifndef config_h
#define config_h

#define DEBUG_MODE 1
#define DEBUG_TIME 0

#define USE_HW_BUTTONS 0

#define MOUSE_POLL_INTERVAL 10 // ms
#define MOUSE_SWAP_INTERVAL 1000 // ms
#define MOUSE_INIT_TRIES 2
#define MOUSE_POLL_TYPE 1 // 1 = poll, 0 = stream

// ---- Pins for Atmega328
#define PIN_KBD_CLK 2 // pin 28 (CLKK)
#define PIN_KBD_DAT 4 // pin 27 (DATK)

#define PIN_MOUSE_CLK 3 // pin 26 (CLKM)
#define PIN_MOUSE_DAT 5 // pin 25 (DATM)

// 13,12,11 - SPI
#define PIN_SCK 13
#define PIN_MISO 12
#define PIN_MOSI 11
#define PIN_SS 7 // SPI slave select

// leds
#define PIN_LED1 A2 // Busy LED
#define PIN_LED2 A1 // Busy LED

// buttons
#define PIN_BTN1 A6
#define PIN_BTN2 A7

// i2c
#define PIN_SDA A4 // pin 23 
#define PIN_SCL A5 // ping 24

// joystick
#define PIN_JOY_UP 6
#define PIN_JOY_DOWN 8
#define PIN_JOY_LEFT 9
#define PIN_JOY_RIGHT 10
#define PIN_JOY_FIRE1 A0
#define PIN_JOY_FIRE2 A3

#define RTC_ADDRESS 0xA0

#define EEPROM_TURBO_ADDRESS 0x00
#define EEPROM_MODE_ADDRESS 0x01
#define EEPROM_SW1_ADDRESS 0x02
#define EEPROM_SW2_ADDRESS 0x03
#define EEPROM_SW3_ADDRESS 0x04
#define EEPROM_SW4_ADDRESS 0x05
#define EEPROM_SW5_ADDRESS 0x06
#define EEPROM_SW6_ADDRESS 0x07
#define EEPROM_SW7_ADDRESS 0x08
#define EEPROM_SW8_ADDRESS 0x09
#define EEPROM_MOUSE_SWAP_ADDRESS 0x0A

#define EEPROM_RTC_OFFSET 0x10

#define EEPROM_VALUE_TRUE 10
#define EEPROM_VALUE_FALSE 20

#endif

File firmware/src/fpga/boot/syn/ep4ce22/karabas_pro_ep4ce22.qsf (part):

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set_global_assignment -name LAST_QUARTUS_VERSION "13.0 SP1"

#==================CLK===========================
set_location_assignment PIN_23 -to CLK_50MHZ

#==================SRAM========================
set_location_assignment PIN_32 -to SRAM_D[0]
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#================= SPI FLASH / SD ===============

#=================MCU===========================
set_location_assignment PIN_54 -to MCU_SCK
set_location_assignment PIN_86 -to MCU_MISO
set_location_assignment PIN_52 -to MCU_MOSI
set_location_assignment PIN_53 -to MCU_CS_N

#=================I2S===========================
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set_location_assignment PIN_125 -to VGA_B[2]
set_location_assignment PIN_121 -to VGA_B[1]
set_location_assignment PIN_120 -to VGA_B[0]
set_location_assignment PIN_119 -to VGA_HS
set_location_assignment PIN_115 -to VGA_VS

#================CPLD===========================
set_location_assignment PIN_114 -to BUS_RESET_N
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set_location_assignment PIN_129 -to BUS_DI[7] # SD15

set_location_assignment PIN_111 -to BUS_DIR
set_location_assignment PIN_55 -to LFDC_STEP

#=================TAPE IN-OUT==================
set_location_assignment PIN_24 -to TAPE_IN

#=================MISC==========================

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

set_location_assignment PIN_25 -to MCU_SD_CS_N
set_location_assignment PIN_8 -to TAPE_OUT
set_global_assignment -name AUTO_RESTART_CONFIGURATION OFF
set_global_assignment -name CYCLONEIII_CONFIGURATION_SCHEME "PASSIVE SERIAL"
set_global_assignment -name GENERATE_RBF_FILE ON
set_location_assignment PIN_6 -to SD_SCK
set_location_assignment PIN_13 -to SD_MISO
set_location_assignment PIN_7 -to SD_MOSI
set_location_assignment PIN_10 -to SD_CS_N
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
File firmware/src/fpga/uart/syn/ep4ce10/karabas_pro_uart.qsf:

# -------------------------------------------------------------------------- #
#
# Copyright (C) 1991-2014 Altera Corporation
# Your use of Altera Corporation's design tools, logic functions 
# and other software and tools, and its AMPP partner logic 
# functions, and any output files from any of the foregoing 
# (including device programming or simulation files), and any 
# associated documentation or information are expressly subject 
# to the terms and conditions of the Altera Program License 
# Subscription Agreement, Altera MegaCore Function License 
# Agreement, or other applicable license agreement, including, 
# without limitation, that your use is for the sole purpose of 
# programming logic devices manufactured by Altera and sold by 
# Altera or its authorized distributors.  Please refer to the 
# applicable agreement for further details.
#
# -------------------------------------------------------------------------- #
#
# Quartus II 32-bit
# Version 13.1.4 Build 182 03/12/2014 SJ Web Edition
# Date created = 12:26:48  August 14, 2017
#
# -------------------------------------------------------------------------- #
#
# Notes:
#
# 1) The default values for assignments are stored in the file:
#		u16_karabas_assignment_defaults.qdf
#    If this file doesn't exist, see file:
#		assignment_defaults.qdf
#
# 2) Altera recommends that you do not modify this file. This
#    file is updated automatically by the Quartus II software
#    and any changes you make may be lost or overwritten.
#
# -------------------------------------------------------------------------- #


set_global_assignment -name FAMILY "Cyclone IV E"
set_global_assignment -name DEVICE EP4CE10E22C8
set_global_assignment -name TOP_LEVEL_ENTITY karabas_pro
set_global_assignment -name ORIGINAL_QUARTUS_VERSION 13.1
set_global_assignment -name PROJECT_CREATION_TIME_DATE "12:26:48  AUGUST 14, 2017"
set_global_assignment -name LAST_QUARTUS_VERSION "13.0 SP1"

#==================CLK===========================
set_location_assignment PIN_23 -to CLK_50MHZ

#=================UART==========================
set_location_assignment PIN_1 -to UART_TX
set_location_assignment PIN_2 -to UART_RX
set_location_assignment PIN_3 -to UART_CTS

#=================BUS=========================

#=================MISC==========================
set_global_assignment -name STRATIX_DEVICE_IO_STANDARD "3.3-V LVTTL"
set_global_assignment -name ENABLE_OCT_DONE OFF
set_global_assignment -name USE_CONFIGURATION_DEVICE ON
set_global_assignment -name CYCLONEIII_CONFIGURATION_DEVICE EPCS16
set_global_assignment -name CRC_ERROR_OPEN_DRAIN OFF
set_global_assignment -name RESERVE_ALL_UNUSED_PINS_WEAK_PULLUP "AS INPUT TRI-STATED"
set_global_assignment -name CYCLONEII_RESERVE_NCEO_AFTER_CONFIGURATION "USE AS REGULAR IO"
set_global_assignment -name RESERVE_DATA0_AFTER_CONFIGURATION "USE AS REGULAR IO"
set_global_assignment -name RESERVE_DATA1_AFTER_CONFIGURATION "USE AS REGULAR IO"
set_global_assignment -name RESERVE_FLASH_NCE_AFTER_CONFIGURATION "USE AS REGULAR IO"
set_global_assignment -name RESERVE_DCLK_AFTER_CONFIGURATION "USE AS REGULAR IO"
set_global_assignment -name OUTPUT_IO_TIMING_NEAR_END_VMEAS "HALF VCCIO" -rise
set_global_assignment -name OUTPUT_IO_TIMING_NEAR_END_VMEAS "HALF VCCIO" -fall
set_global_assignment -name OUTPUT_IO_TIMING_FAR_END_VMEAS "HALF SIGNAL SWING" -rise
set_global_assignment -name OUTPUT_IO_TIMING_FAR_END_VMEAS "HALF SIGNAL SWING" -fall
set_global_assignment -name POWER_PRESET_COOLING_SOLUTION "23 MM HEAT SINK WITH 200 LFPM AIRFLOW"
set_global_assignment -name POWER_BOARD_THERMAL_MODEL "NONE (CONSERVATIVE)"
set_global_assignment -name SYNTH_TIMING_DRIVEN_SYNTHESIS ON

set_global_assignment -name PARTITION_NETLIST_TYPE SOURCE -section_id Top
set_global_assignment -name PARTITION_FITTER_PRESERVATION_LEVEL PLACEMENT_AND_ROUTING -section_id Top
set_global_assignment -name PARTITION_COLOR 16764057 -section_id Top
set_global_assignment -name MIN_CORE_JUNCTION_TEMP 0
set_global_assignment -name MAX_CORE_JUNCTION_TEMP 85

set_global_assignment -name PHYSICAL_SYNTHESIS_ASYNCHRONOUS_SIGNAL_PIPELINING ON
set_global_assignment -name PHYSICAL_SYNTHESIS_REGISTER_DUPLICATION ON
set_global_assignment -name PHYSICAL_SYNTHESIS_COMBO_LOGIC_FOR_AREA ON
set_global_assignment -name PHYSICAL_SYNTHESIS_MAP_LOGIC_TO_MEMORY_FOR_AREA ON
set_global_assignment -name CYCLONEII_OPTIMIZATION_TECHNIQUE AREA
set_global_assignment -name ALLOW_POWER_UP_DONT_CARE OFF
set_instance_assignment -name GLOBAL_SIGNAL "GLOBAL CLOCK" -to CLK_50MHZ



set_global_assignment -name EDA_GENERATE_FUNCTIONAL_NETLIST OFF -section_id eda_formal_verification

set_global_assignment -name OPTIMIZE_HOLD_TIMING "ALL PATHS"
set_global_assignment -name OPTIMIZE_MULTI_CORNER_TIMING ON


set_global_assignment -name VHDL_FILE ../../rtl/karabas_pro.vhd

set_global_assignment -name CDF_FILE karabas_pro_ep4ce10.cdf

set_location_assignment PIN_141 -to UART2_TX
set_location_assignment PIN_138 -to UART2_CTS
set_location_assignment PIN_25 -to UART2_RX
set_instance_assignment -name PARTITION_HIERARCHY root_partition -to | -section_id Top
